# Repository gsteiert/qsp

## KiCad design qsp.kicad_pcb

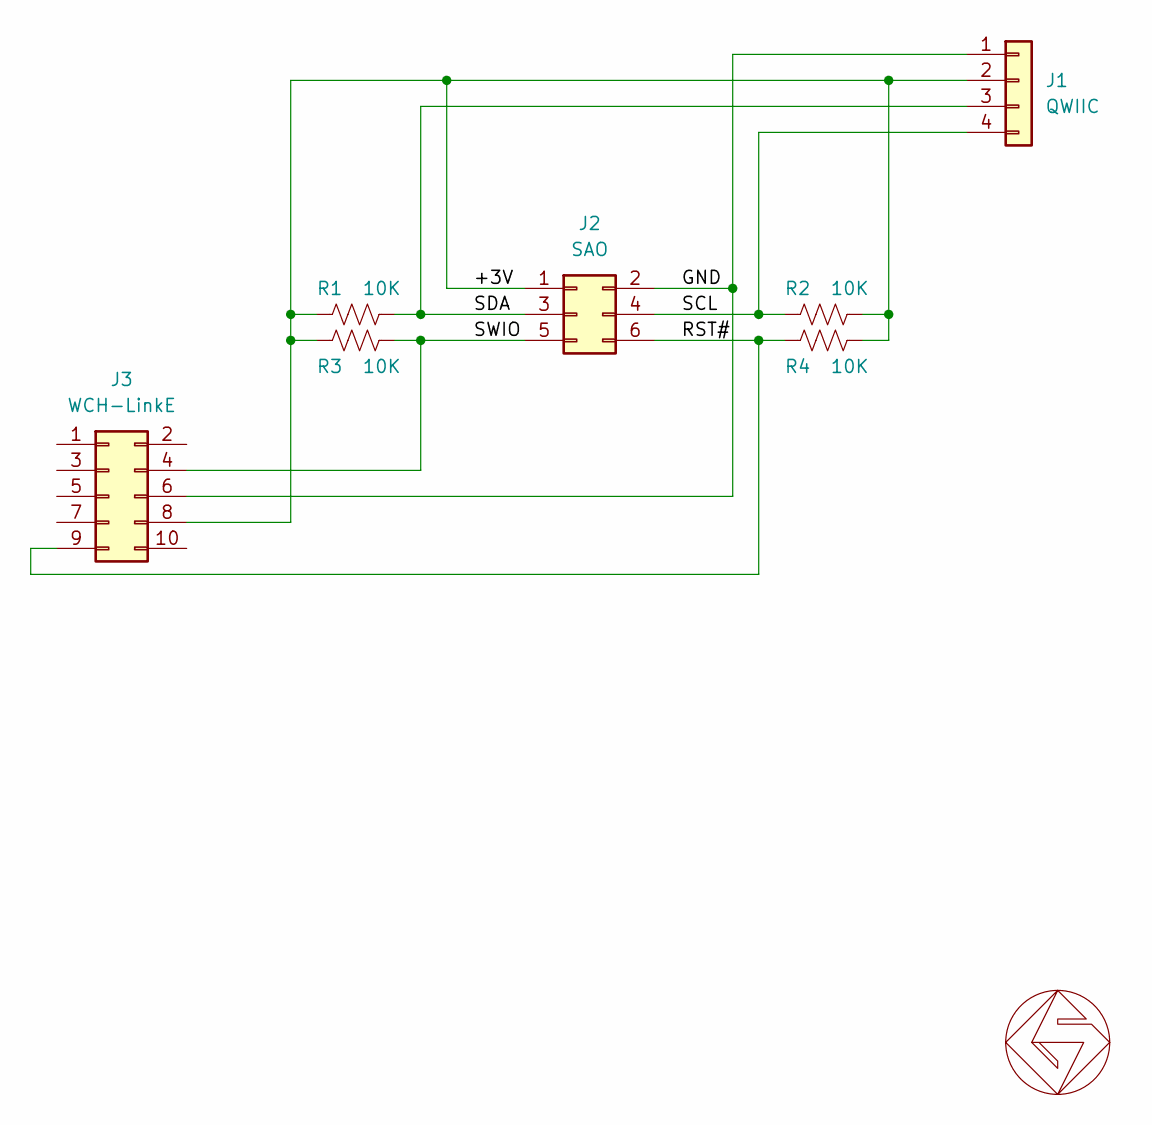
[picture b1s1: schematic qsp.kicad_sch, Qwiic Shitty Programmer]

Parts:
GS1: GS_logo; gs_logo_200mil
J1: QWIIC; JST_SH_SM04B-SRSS-TB_1x04-1MP_P1.00mm_Horizontal
J2: SAO; PinHeader_2x03_P2.54mm_Vertical
J3: WCH-LinkE; PinSocket_2x05_P2.54mm_Horizontal
R1, R2, R3, R4: 10K; R_0603_1608Metric

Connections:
/+3V: J1.2, J2.1, J3.8, R1.1, R2.2, R3.1, R4.2
/GND: J1.1, J2.2, J3.6
/RST#: J2.6, J3.9, R4.1
/SCL: J1.4, J2.4, R2.1
/SDA: J1.3, J2.3, R1.2
/SWIO: J2.5, J3.4, R3.2

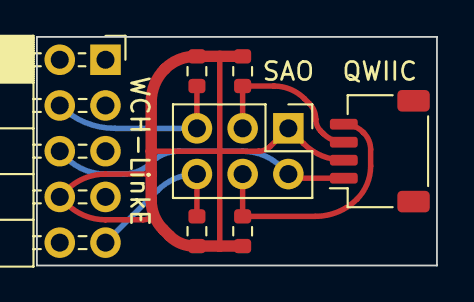
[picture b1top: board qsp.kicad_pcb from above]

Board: 2 copper layers, 22.2 x 12.7 mm, 8 parts (1 on the bottom side), 6 nets.
